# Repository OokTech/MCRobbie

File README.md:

# MCRobbie

See more in-depth documentation on the [official documentation site](https://ooktech.com/Documentation/MCRobbie/).

What is it?

An advanced motor controller with an i2c interface.

That means it is something that you connect to using an i2c interface and it generates the control signals needed by the motor drivers for up to 4 motors. The 'advanced' part is because the controller can take care of acceleration for your motors. So if you are using this to control the wheels of a robot (which is the original application that it was designed for) than you can just send the desired speed and the controller can take care of accelerating to that speed so that the robot moves smoothly.

The controller can provide signals to control up to 4 motors independently. The motor drivers can be either 2- or 3- wire drivers.

## Why would I use this?

You may want to use this if you:

- have a limited number of pins for control on your project
- not have enough pins on your Arduino to run as many motors as you need
- want to control motors from a raspberry pi
- want your motors to accelerate without adding programming overhead
- want to use the i2c interface on your controller
- want your control signals to be cleaner than the signals generated by the normal Arduino libraries (see note below)

You may not want to use this if you:

- have plenty of pins
- don't want your motors to do anything other than move at one speed
- don't have an i2c interface on your controller
- have no way to program the controller or to buy a programmed one

### Note about Arduino:

The Arduino libraries and boards have worked very well for us. We made this because it is much less expensive (an uno costs about 20 euro, the PIC used costs around 2 euro), the control signals generated by Arduinos have been somewhat inconsistent when rapidly changing motor speed, and, the PIC is much smaller than the Ardunio boards and we can integrate it into our custom PCB designs.

## How do I use this?

We are in the process of creating detailed tutorials.

At the moment the only hardware this has been tested on is a PIC18f14k50 controller. It is an 8-bit microcontroller sold by microchip. If you have a compatible programmer (I am using the PICKit 3) you can just load this code and program the controller normally. If you order from microchip they can program the device before sending it to you, although I have not yet tried this.

This same code should work without changes on the PIC18f14k22, and possibly on other PIC18 chips, but that has not yet been tested. One of our priorities now is to port this code onto some Atmel chips that can be programmed using an Arduino, and into code that can be put on an Arduino directly. The purpose of this controller is that it is very cheap (about 2 euro for the chip and it doesn't require any external components), a lot of people have Arduinos already so using one could be a cheaper option for some.

# An important note

This is a controller, not a driver. The controller generates the signals needed to make a motor move in the direction and at the speed you want, a motor driver is needed to supply the power to the motor.

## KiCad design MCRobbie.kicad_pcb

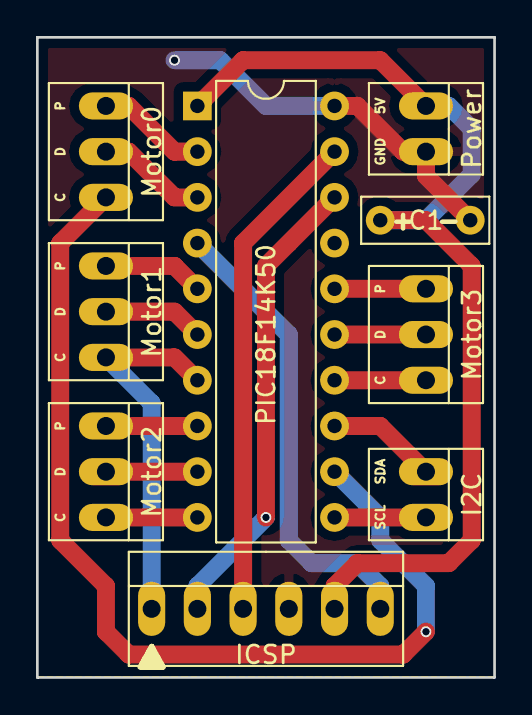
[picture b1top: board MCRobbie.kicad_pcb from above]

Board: 2 copper layers, 25.4 x 35.6 mm, 9 parts (0 on the bottom side), 19 nets.

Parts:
C1: C_Rect_L7.0mm_W2.5mm_P5.00mm
I2C: I2C_Header; PINHEAD1-2
ICSP: ICP_Header; PINHEAD1-6
Motor0: Motor0; PINHEAD1-3
Motor1: Motor1; PINHEAD1-3
Motor2: Motor2; PINHEAD1-3
Motor3: Motor3; PINHEAD1-3
PIC18F14K50: PIC18F14K50; DIP-20_W7.62mm
Power: Power_Header; PINHEAD1-2

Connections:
+5V: C1.1, ICSP.5, PIC18F14K50.1, Power.1
GND: C1.2, ICSP.4, PIC18F14K50.20, Power.2
unnamed: Motor0.1, PIC18F14K50.2
unnamed: Motor0.2, PIC18F14K50.3
unnamed: Motor0.3, PIC18F14K50.12
unnamed: Motor1.1, PIC18F14K50.5
unnamed: Motor1.2, PIC18F14K50.6
unnamed: ICSP.1, Motor1.3, PIC18F14K50.7
unnamed: Motor2.1, PIC18F14K50.8
unnamed: Motor2.2, PIC18F14K50.9
unnamed: Motor2.3, PIC18F14K50.10
unnamed: Motor3.1, PIC18F14K50.16
unnamed: Motor3.2, PIC18F14K50.15
unnamed: Motor3.3, PIC18F14K50.14
unnamed: I2C.1, PIC18F14K50.13
unnamed: I2C.2, PIC18F14K50.11
unnamed: ICSP.2, PIC18F14K50.18
unnamed: ICSP.3, PIC18F14K50.19
unnamed: ICSP.6, PIC18F14K50.4

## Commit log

2017-06-04 Too many updates to count, it works well
2017-06-04 Even more updates, added servo control too
2017-06-05 The 3-wire motors work, so the 2-wire should also. Still haven't tested servos
2017-06-06 Pinouts are now consistent for all motors
2017-06-09 Added some more documentation
2017-06-15 Now everything is configurable, also no signed-unsigned warnings
2017-06-16 Removing unneeded files from the repo
2017-06-16 Everything is initialised correctly now
2017-06-16 Add license file and headers to everything
2017-06-16 Added README.md
2017-06-16 Removed .DS_Store again
    pay attention next time
2017-06-16 Added kicad pcb file
2017-06-18 Added pcb and schematic to repo
2017-07-06 You can now read bytes in sequence over I2C and other improvements
    You can read the target speed value instead of just the current pwm output value
    Exponential acceleration is now default
    The pwm now uses a significantly slower frequency because we were getting way too much jitter before and sometimes missing pulses completely
2017-07-07 Added i2c access to the targetDirection registers

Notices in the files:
MCRobbie.kicad_pcb:
Copyright OokTech CC-BY-SA
